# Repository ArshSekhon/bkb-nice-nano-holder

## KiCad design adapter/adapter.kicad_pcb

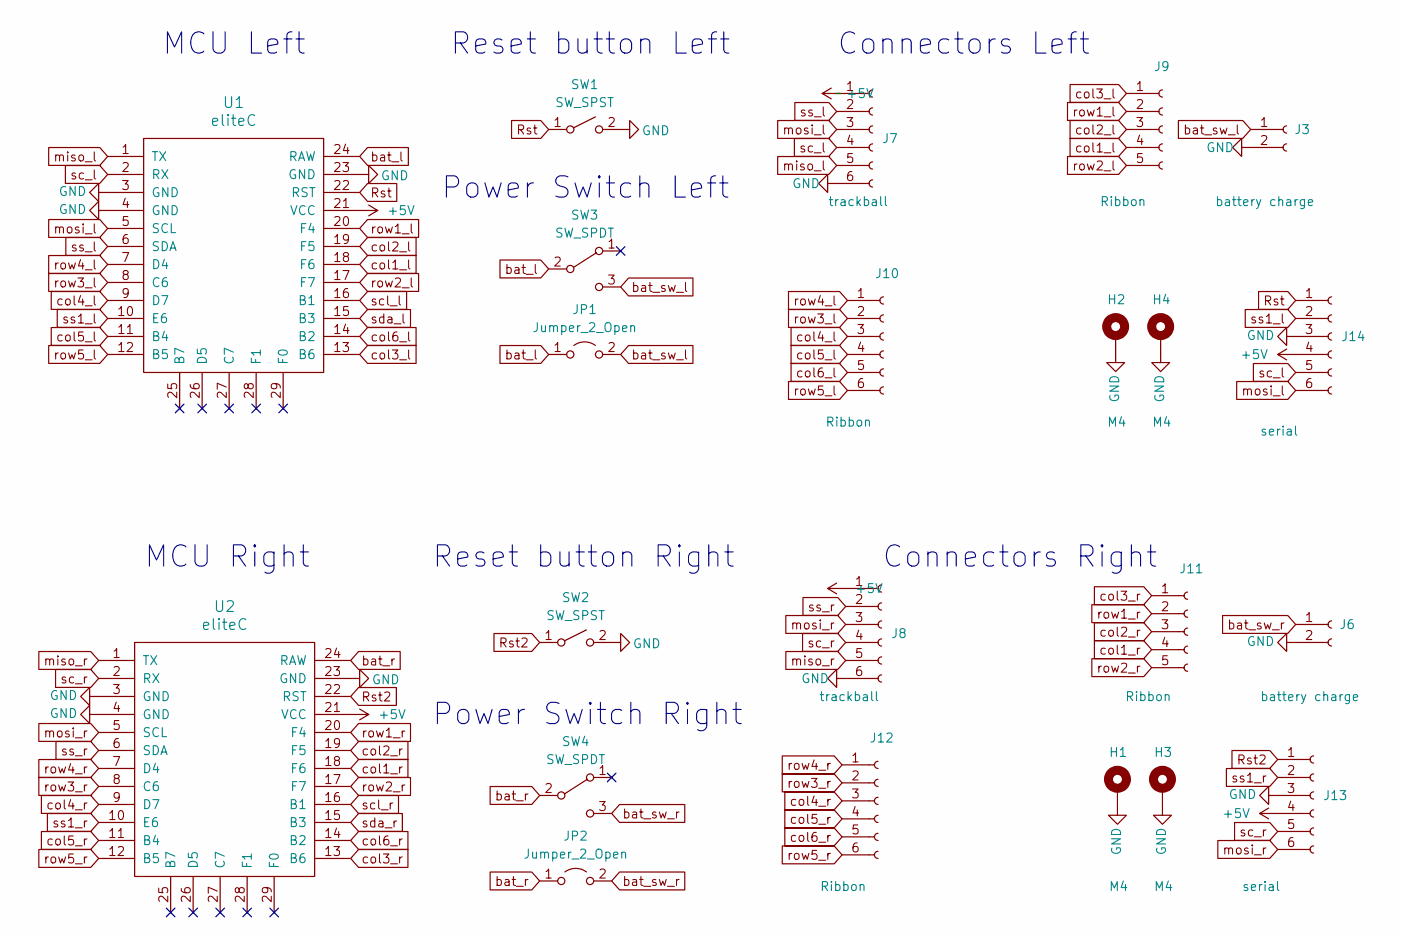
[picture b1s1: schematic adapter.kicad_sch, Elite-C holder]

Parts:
H1, H2, H3, H4: M4; MountingHole_4mm_Pad_thin
J3, J6: battery charge; JST_PH_B2B-PH-K_1x02_P2.00mm_Vertical
J7, J8: trackball; 6_PinHeader
J9, J11: Ribbon; 5_PinHeader
J10, J12: Ribbon; 6_PinHeader
J13: serial; PinSocket_1x06_P2.54mm_Vertical
J14: serial; PinHeader_1x06_P2.54mm_Vertical
JP1, JP2: Jumper_2_Open; power_switch_jumper
SW1, SW2: SW_SPST; PushSwitch
SW3, SW4: SW_SPDT; SW_SPDT+H-MSK12C01_hor(7pin_SMD)
U1, U2: eliteC; Elite-C

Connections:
+5V: J7.1, J8.1, J13.4, J14.4, U1.21 (VCC), U2.21 (VCC)
GND: H1.1, H2.1, H3.1, H4.1, J3.2, J6.2, J7.6, J8.6, J13.3, J14.3, SW1.2 (B), SW2.2 (B), U1.3 (GND), U1.4 (GND), U1.23 (GND), U2.3 (GND), U2.4 (GND), U2.23 (GND)
Rst: J14.1, SW1.1 (A), U1.22 (RST)
Rst2: J13.1, SW2.1 (A), U2.22 (RST)
bat_l: JP1.1 (A), SW3.2 (B), U1.24 (RAW)
bat_r: JP2.1 (A), SW4.2 (B), U2.24 (RAW)
bat_sw_l: J3.1, JP1.2 (B), SW3.3 (C)
bat_sw_r: J6.1, JP2.2 (B), SW4.3 (C)
col1_l: J9.4, U1.18 (F6)
col1_r: J11.4, U2.18 (F6)
col2_l: J9.3, U1.19 (F5)
col2_r: J11.3, U2.19 (F5)
col3_l: J9.1, U1.13 (B6)
col3_r: J11.1, U2.13 (B6)
col4_l: J10.3, U1.9 (D7)
col4_r: J12.3, U2.9 (D7)
col5_l: J10.4, U1.11 (B4)
col5_r: J12.4, U2.11 (B4)
col6_l: J10.5, U1.14 (B2)
col6_r: J12.5, U2.14 (B2)
miso_l: J7.5, U1.1 (TX)
miso_r: J8.5, U2.1 (TX)
mosi_l: J7.3, J14.6, U1.5 (SCL)
mosi_r: J8.3, J13.6, U2.5 (SCL)
row1_l: J9.2, U1.20 (F4)
row1_r: J11.2, U2.20 (F4)
row2_l: J9.5, U1.17 (F7)
row2_r: J11.5, U2.17 (F7)
row3_l: J10.2, U1.8 (C6)
row3_r: J12.2, U2.8 (C6)
row4_l: J10.1, U1.7 (D4)
row4_r: J12.1, U2.7 (D4)
row5_l: J10.6, U1.12 (B5)
row5_r: J12.6, U2.12 (B5)
sc_l: J7.4, J14.5, U1.2 (RX)
sc_r: J8.4, J13.5, U2.2 (RX)
scl_l: U1.16 (B1)
scl_r: U2.16 (B1)
sda_l: U1.15 (B3)
sda_r: U2.15 (B3)
ss1_l: J14.2, U1.10 (E6)
ss1_r: J13.2, U2.10 (E6)
ss_l: J7.2, U1.6 (SDA)
ss_r: J8.2, U2.6 (SDA)

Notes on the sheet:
Power Switch Right
Reset button Left
Power Switch Left
Connectors Left
Reset button Right
MCU Left
MCU Right
Connectors Right

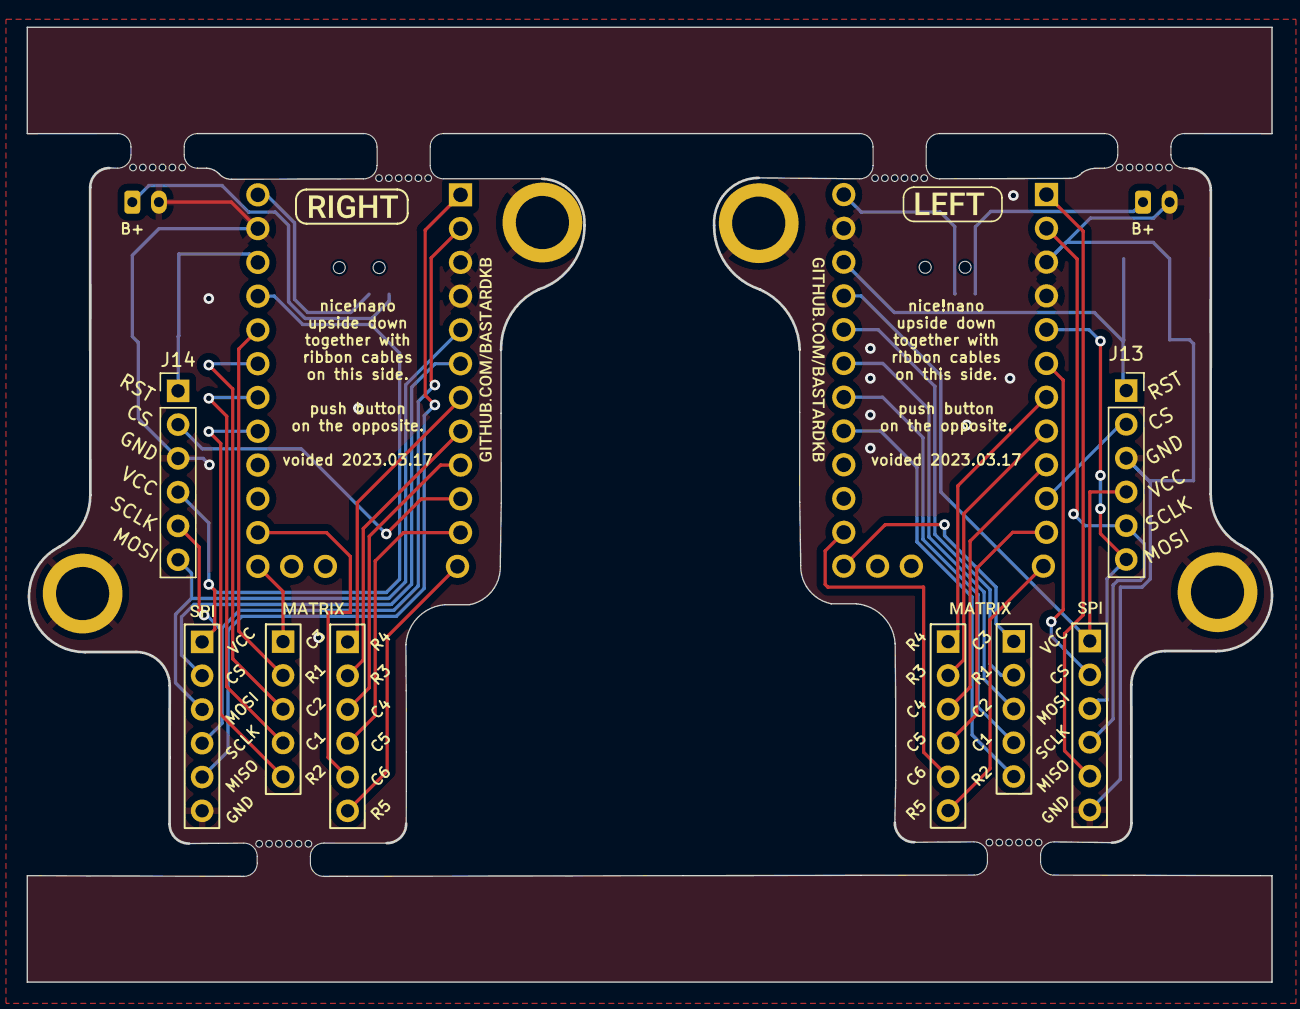
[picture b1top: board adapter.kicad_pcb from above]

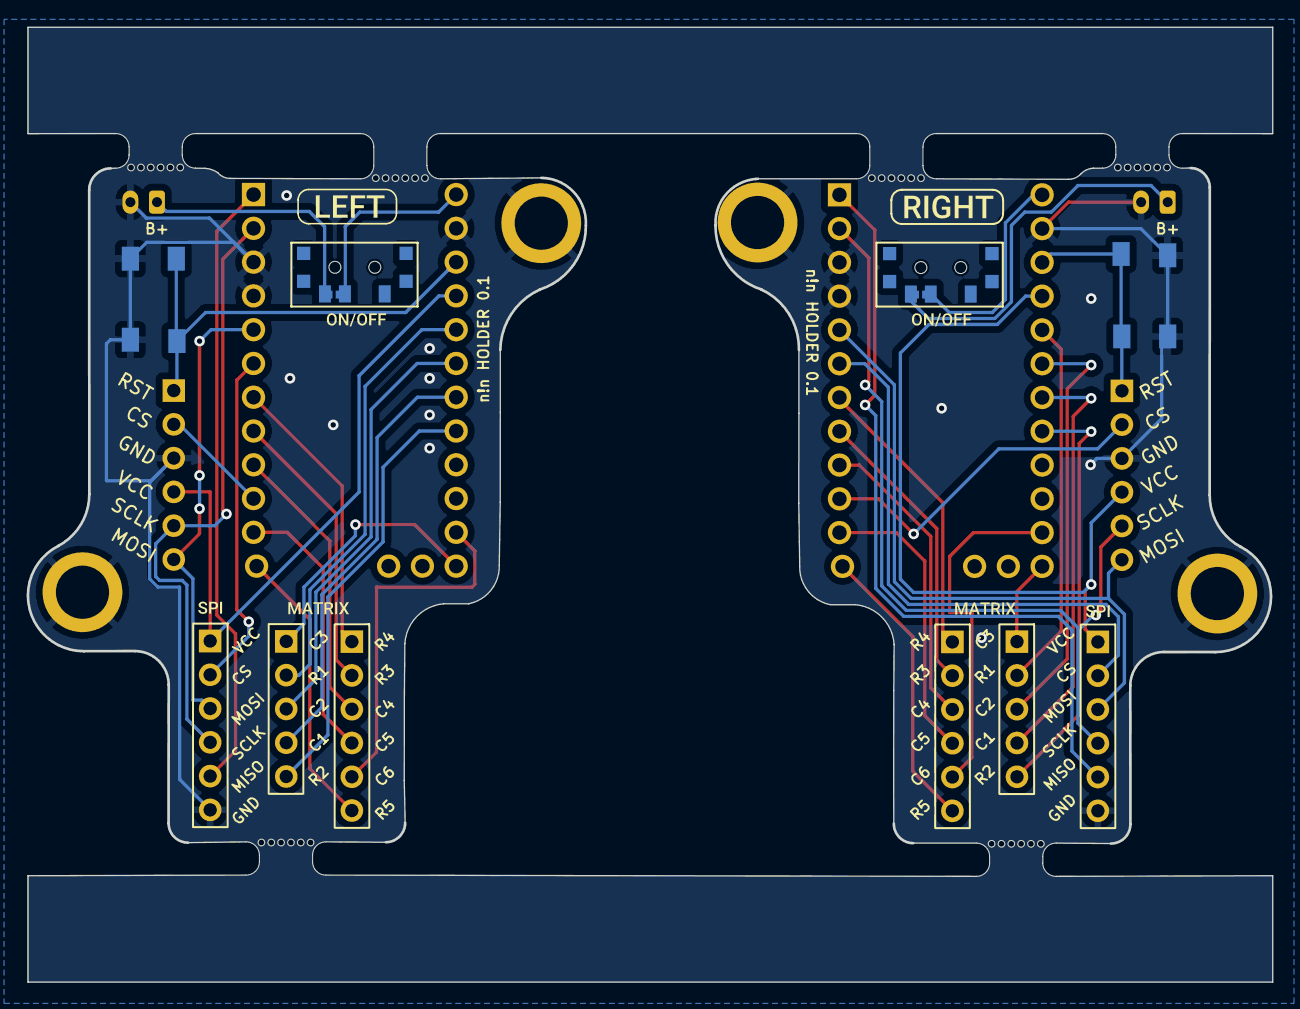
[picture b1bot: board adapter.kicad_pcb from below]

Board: 2 copper layers, 93.6 x 71.7 mm, 38 parts (16 on the bottom side), 40 nets.

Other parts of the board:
kibuzzard-61F01A92, kibuzzard-61F01A92#2: G***; kibuzzard-61F01A92
kibuzzard-61F01B61, kibuzzard-61F01B61#2: G***; kibuzzard-61F01B61
kibuzzard-61F01940, kibuzzard-61F01940#2, kibuzzard-61F01940#3, kibuzzard-61F01940#4: G***; kibuzzard-61F01940
kibuzzard-61F01957, kibuzzard-61F01957#2, kibuzzard-61F01957#3, kibuzzard-61F01957#4: G***; kibuzzard-61F01957
kibuzzard-620B8593, kibuzzard-620B8593#2: G***; kibuzzard-620B8593
kibuzzard-6208EFFE, kibuzzard-6208EFFE#2: G***; kibuzzard-6208EFFE

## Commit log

2023-12-20 Intial Commit
2023-12-25 fixed col6 and gnd fills

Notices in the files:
adapter/adapter.kicad_sch:
Licensed under CERN-OHL-W v2
